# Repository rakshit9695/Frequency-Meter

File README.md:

# Frequency-Meter

## Overview

The **Frequency Meter** is a digital circuit designed to measure an unknown input frequency in the range of **0.00 Hz to 99.99 Hz**. It operates using a **100 Hz Time Base Frequency** as a reference for measurement accuracy.

This project includes both the schematic and PCB design created using **KiCad**. The design is compact and intended for educational or experimental use in lab environments or as a standalone frequency counter module.

---

## Features

- Measures frequency in the range **0.00 Hz to 99.99 Hz**
- **100 Hz Time Base** for accurate measurement
- Dual-digit decimal output display
- Optimized for simplicity and low component count
- Designed in KiCad (open-source EDA)

---

## How It Works

The working principle is based on frequency counting using a time gate. The **unknown signal** is counted over a **fixed time window of 1 second** (derived from a 100 Hz time base using a divider circuit). The counted pulses are then scaled and displayed on a 2-digit 7-segment display, showing values in the format XX.XX.

### Major Blocks:

- **Time Base Generator**: Generates 100 Hz from a crystal oscillator or other stable reference.
- **Frequency Counter Logic**: Counts the number of pulses from the unknown frequency source during the gate time.
- **Display Driver**: Converts the counted value into a human-readable format using 7-segment displays.

---

## Schematic and PCB

- **Schematic File**: `0682.kicad_sch`
- **PCB Layout File**: `0682.kicad_pcb`

These files can be opened using [KiCad](https://www.kicad.org/) (version 6 or later recommended).

---

## Components Used (Typical)

- Crystal Oscillator or Timer IC (for 100 Hz base)
- Flip-flops / Logic ICs (74-series or CD4000)
- Counters (e.g., CD4017, 74LS90)
- 7-Segment Display Drivers
- 7-Segment Displays (2-digit)
- Resistors, Capacitors, and other passive components
- Optional: Microcontroller (if using software counter)

---

## Applications

- Frequency counter for waveform generators
- Educational kits and demonstrations
- DIY electronics lab equipment
- Signal analysis and debugging tools

---

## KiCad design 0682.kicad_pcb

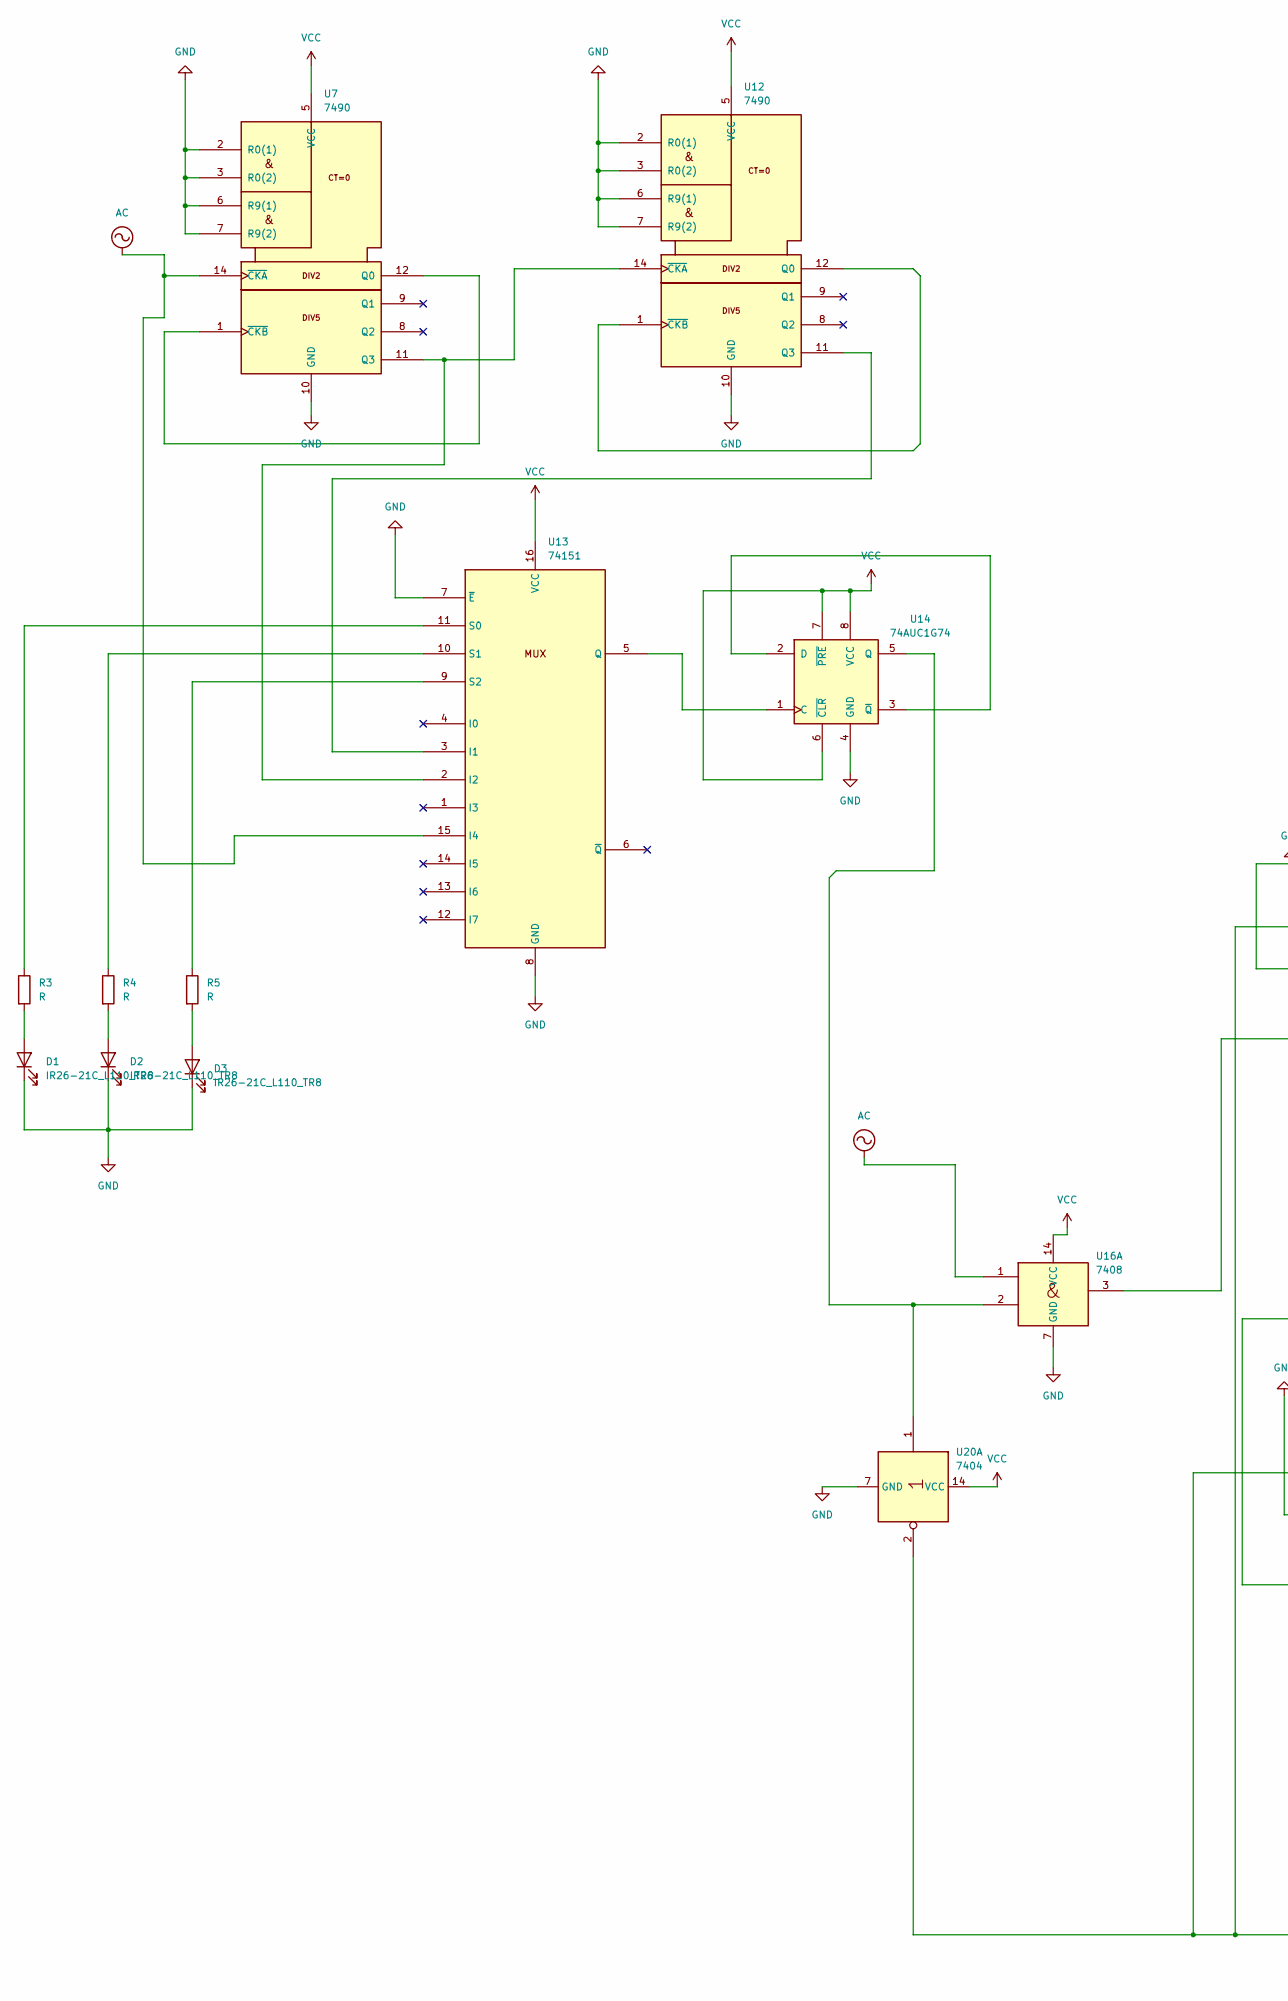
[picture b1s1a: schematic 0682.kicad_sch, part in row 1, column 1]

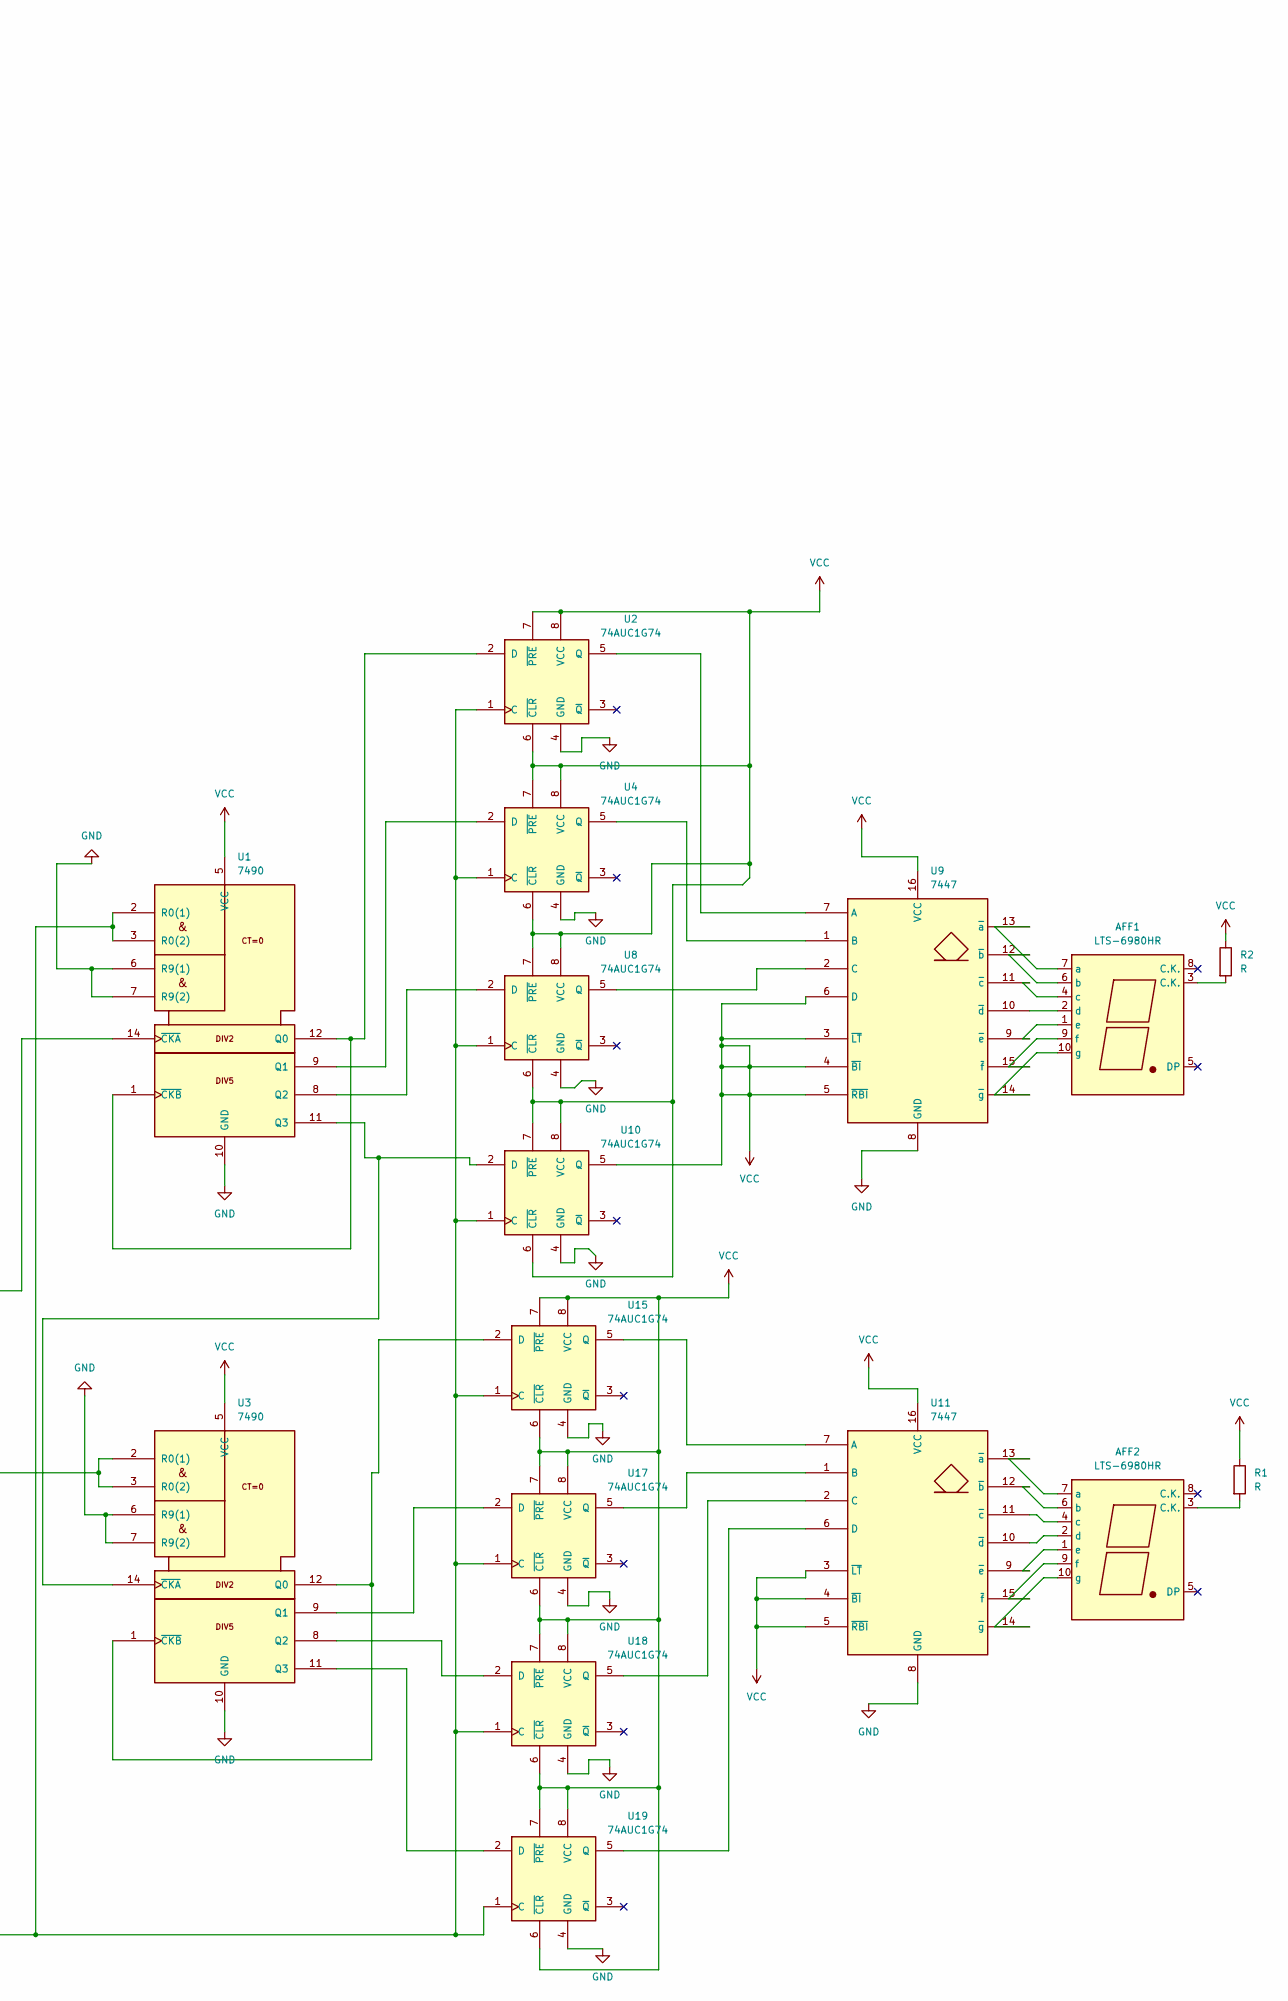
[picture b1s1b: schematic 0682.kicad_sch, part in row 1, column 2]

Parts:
AFF1, AFF2: LTS-6980HR; 7SegmentLED_LTS6760_LTS6780
D1, D2, D3: IR26-21C_L110_TR8; LED_1206_3216Metric
R1, R2, R3, R4, R5: R; R_0201_0603Metric
U1, U3, U7, U12: 7490; DIP254P762X508-14
U2, U4, U8, U10, U14, U15, U17, U18, U19: 74AUC1G74; SOP50P310X90-8N
U9, U11: 7447; DIP794W45P254L1969H508Q16
U13: 74151; DIP762W46P254L1930H508Q16
U16: 7408; DIP794W45P254L1969H508Q14
U20: 7404; DIP794W45P254L1969H508Q14

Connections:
AC: U7.14 (~CKA), U13.15 (I4), U16.1
GND: D1.1 (K), D2.1 (K), D3.1 (K), U1.6 (R9(1)), U1.7 (R9(2)), U1.10 (GND), U2.4 (GND), U3.6 (R9(1)), U3.7 (R9(2)), U3.10 (GND), U4.4 (GND), U7.2 (R0(1)), U7.3 (R0(2)), U7.6 (R9(1)), U7.7 (R9(2)), U7.10 (GND), U8.4 (GND), U9.8 (GND), U10.4 (GND), U11.8 (GND), U12.2 (R0(1)), U12.3 (R0(2)), U12.6 (R9(1)), U12.7 (R9(2)), U12.10 (GND), U13.7 (~E), U13.8 (GND), U14.4 (GND), U15.4 (GND), U16.7 (GND), U17.4 (GND), U18.4 (GND), U19.4 (GND), U20.7 (GND)
unnamed: AFF1.3 (C.K.), R2.2
unnamed: AFF1.7 (a), U9.13 (~a)
unnamed: AFF1.6 (b), U9.12 (~b)
unnamed: AFF1.4 (c), U9.11 (~c)
unnamed: AFF1.2 (d), U9.10 (~d)
unnamed: AFF1.1 (e), U9.9 (~e)
unnamed: AFF1.9 (f), U9.15 (~f)
unnamed: AFF1.10 (g), U9.14 (~g)
unnamed: AFF2.3 (C.K.), R1.2
unnamed: AFF2.7 (a), U11.13 (~a)
unnamed: AFF2.6 (b), U11.12 (~b)
unnamed: AFF2.4 (c), U11.11 (~c)
unnamed: AFF2.2 (d), U11.10 (~d)
unnamed: AFF2.1 (e), U11.9 (~e)
unnamed: AFF2.9 (f), U11.15 (~f)
unnamed: AFF2.10 (g), U11.14 (~g)
unnamed: D1.2 (A), R3.2
unnamed: D2.2 (A), R4.2
unnamed: D3.2 (A), R5.2
unnamed: U1.1 (~CKB), U1.12 (Q0), U2.2 (D)
unnamed: U1.9 (Q1), U4.2 (D)
unnamed: U1.8 (Q2), U8.2 (D)
unnamed: U1.11 (Q3), U3.14 (~CKA), U10.2 (D)
unnamed: U1.2 (R0(1)), U1.3 (R0(2)), U2.1 (C), U3.2 (R0(1)), U3.3 (R0(2)), U4.1 (C), U8.1 (C), U10.1 (C), U15.1 (C), U17.1 (C), U18.1 (C), U19.1 (C), U20.2
unnamed: U1.14 (~CKA), U16.3
unnamed: U2.5 (Q), U9.7 (A)
unnamed: U4.5 (Q), U9.1 (B)
unnamed: U7.1 (~CKB), U7.12 (Q0)
unnamed: U8.5 (Q), U9.2 (C)
unnamed: U11.7 (A), U15.5 (Q)
unnamed: U11.1 (B), U17.5 (Q)
unnamed: U11.2 (C), U18.5 (Q)
unnamed: U11.6 (D), U19.5 (Q)
unnamed: U12.1 (~CKB), U12.12 (Q0)
unnamed: U12.11 (Q3), U13.3 (I1)
unnamed: U7.11 (Q3), U12.14 (~CKA), U13.2 (I2)
unnamed: U13.5 (Q), U14.1 (C)
unnamed: R3.1, U13.11 (S0)
unnamed: R4.1, U13.10 (S1)
unnamed: R5.1, U13.9 (S2)
unnamed: U14.2 (D), U14.3 (~Q)
unnamed: U14.5 (Q), U16.2, U20.1
unnamed: U3.1 (~CKB), U3.12 (Q0), U15.2 (D)
unnamed: U3.9 (Q1), U17.2 (D)
unnamed: U3.8 (Q2), U18.2 (D)
unnamed: U3.11 (Q3), U19.2 (D)
VCC: R1.1, R2.1, U1.5 (VCC), U2.6 (~CLR), U2.7 (~PRE), U2.8 (VCC), U3.5 (VCC), U4.6 (~CLR), U4.7 (~PRE), U4.8 (VCC), U7.5 (VCC), U8.6 (~CLR), U8.7 (~PRE), U8.8 (VCC), U9.3 (~LT), U9.4 (~BI), U9.5 (~RBI), U9.6 (D), U9.16 (VCC), U10.5 (Q), U10.6 (~CLR), U10.7 (~PRE), U10.8 (VCC), U11.3 (~LT), U11.4 (~BI), U11.5 (~RBI), U11.16 (VCC), U12.5 (VCC), U13.16 (VCC), U14.6 (~CLR), U14.7 (~PRE), U14.8 (VCC), U15.6 (~CLR), U15.7 (~PRE), U15.8 (VCC), U16.14 (VCC), U17.6 (~CLR), U17.7 (~PRE), U17.8 (VCC), U18.6 (~CLR), U18.7 (~PRE), U18.8 (VCC), U19.6 (~CLR), U19.7 (~PRE), U19.8 (VCC), U20.14 (VCC)

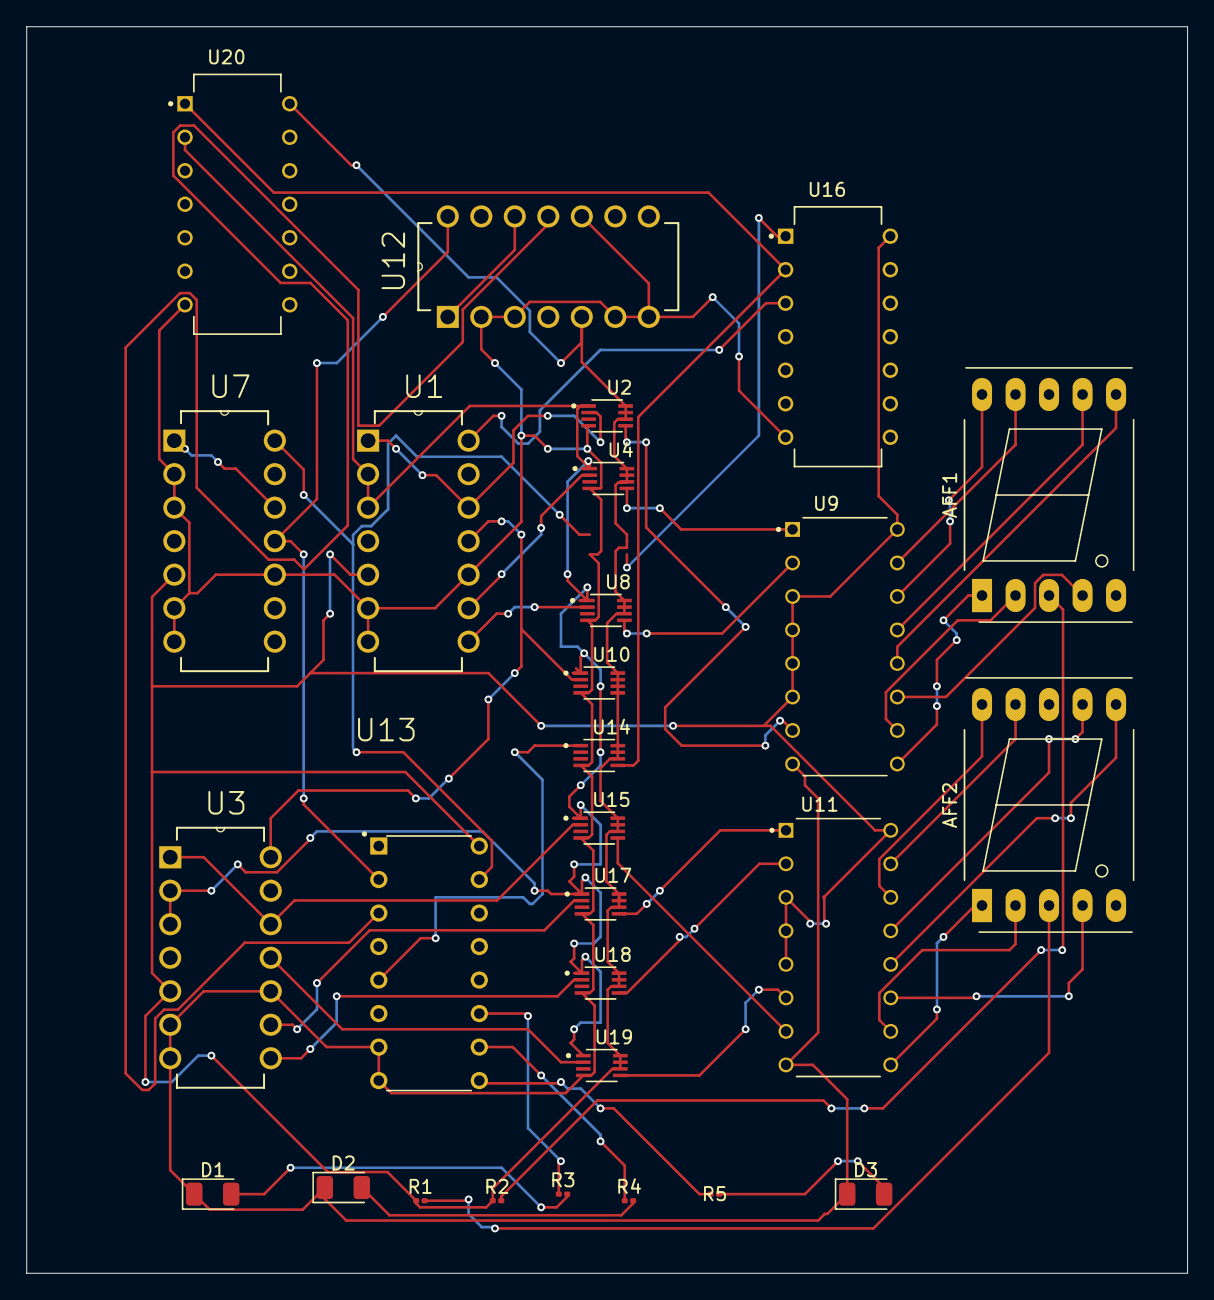
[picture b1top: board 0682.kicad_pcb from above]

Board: 2 copper layers, 88.0 x 94.5 mm, 28 parts (0 on the bottom side), 49 nets.
